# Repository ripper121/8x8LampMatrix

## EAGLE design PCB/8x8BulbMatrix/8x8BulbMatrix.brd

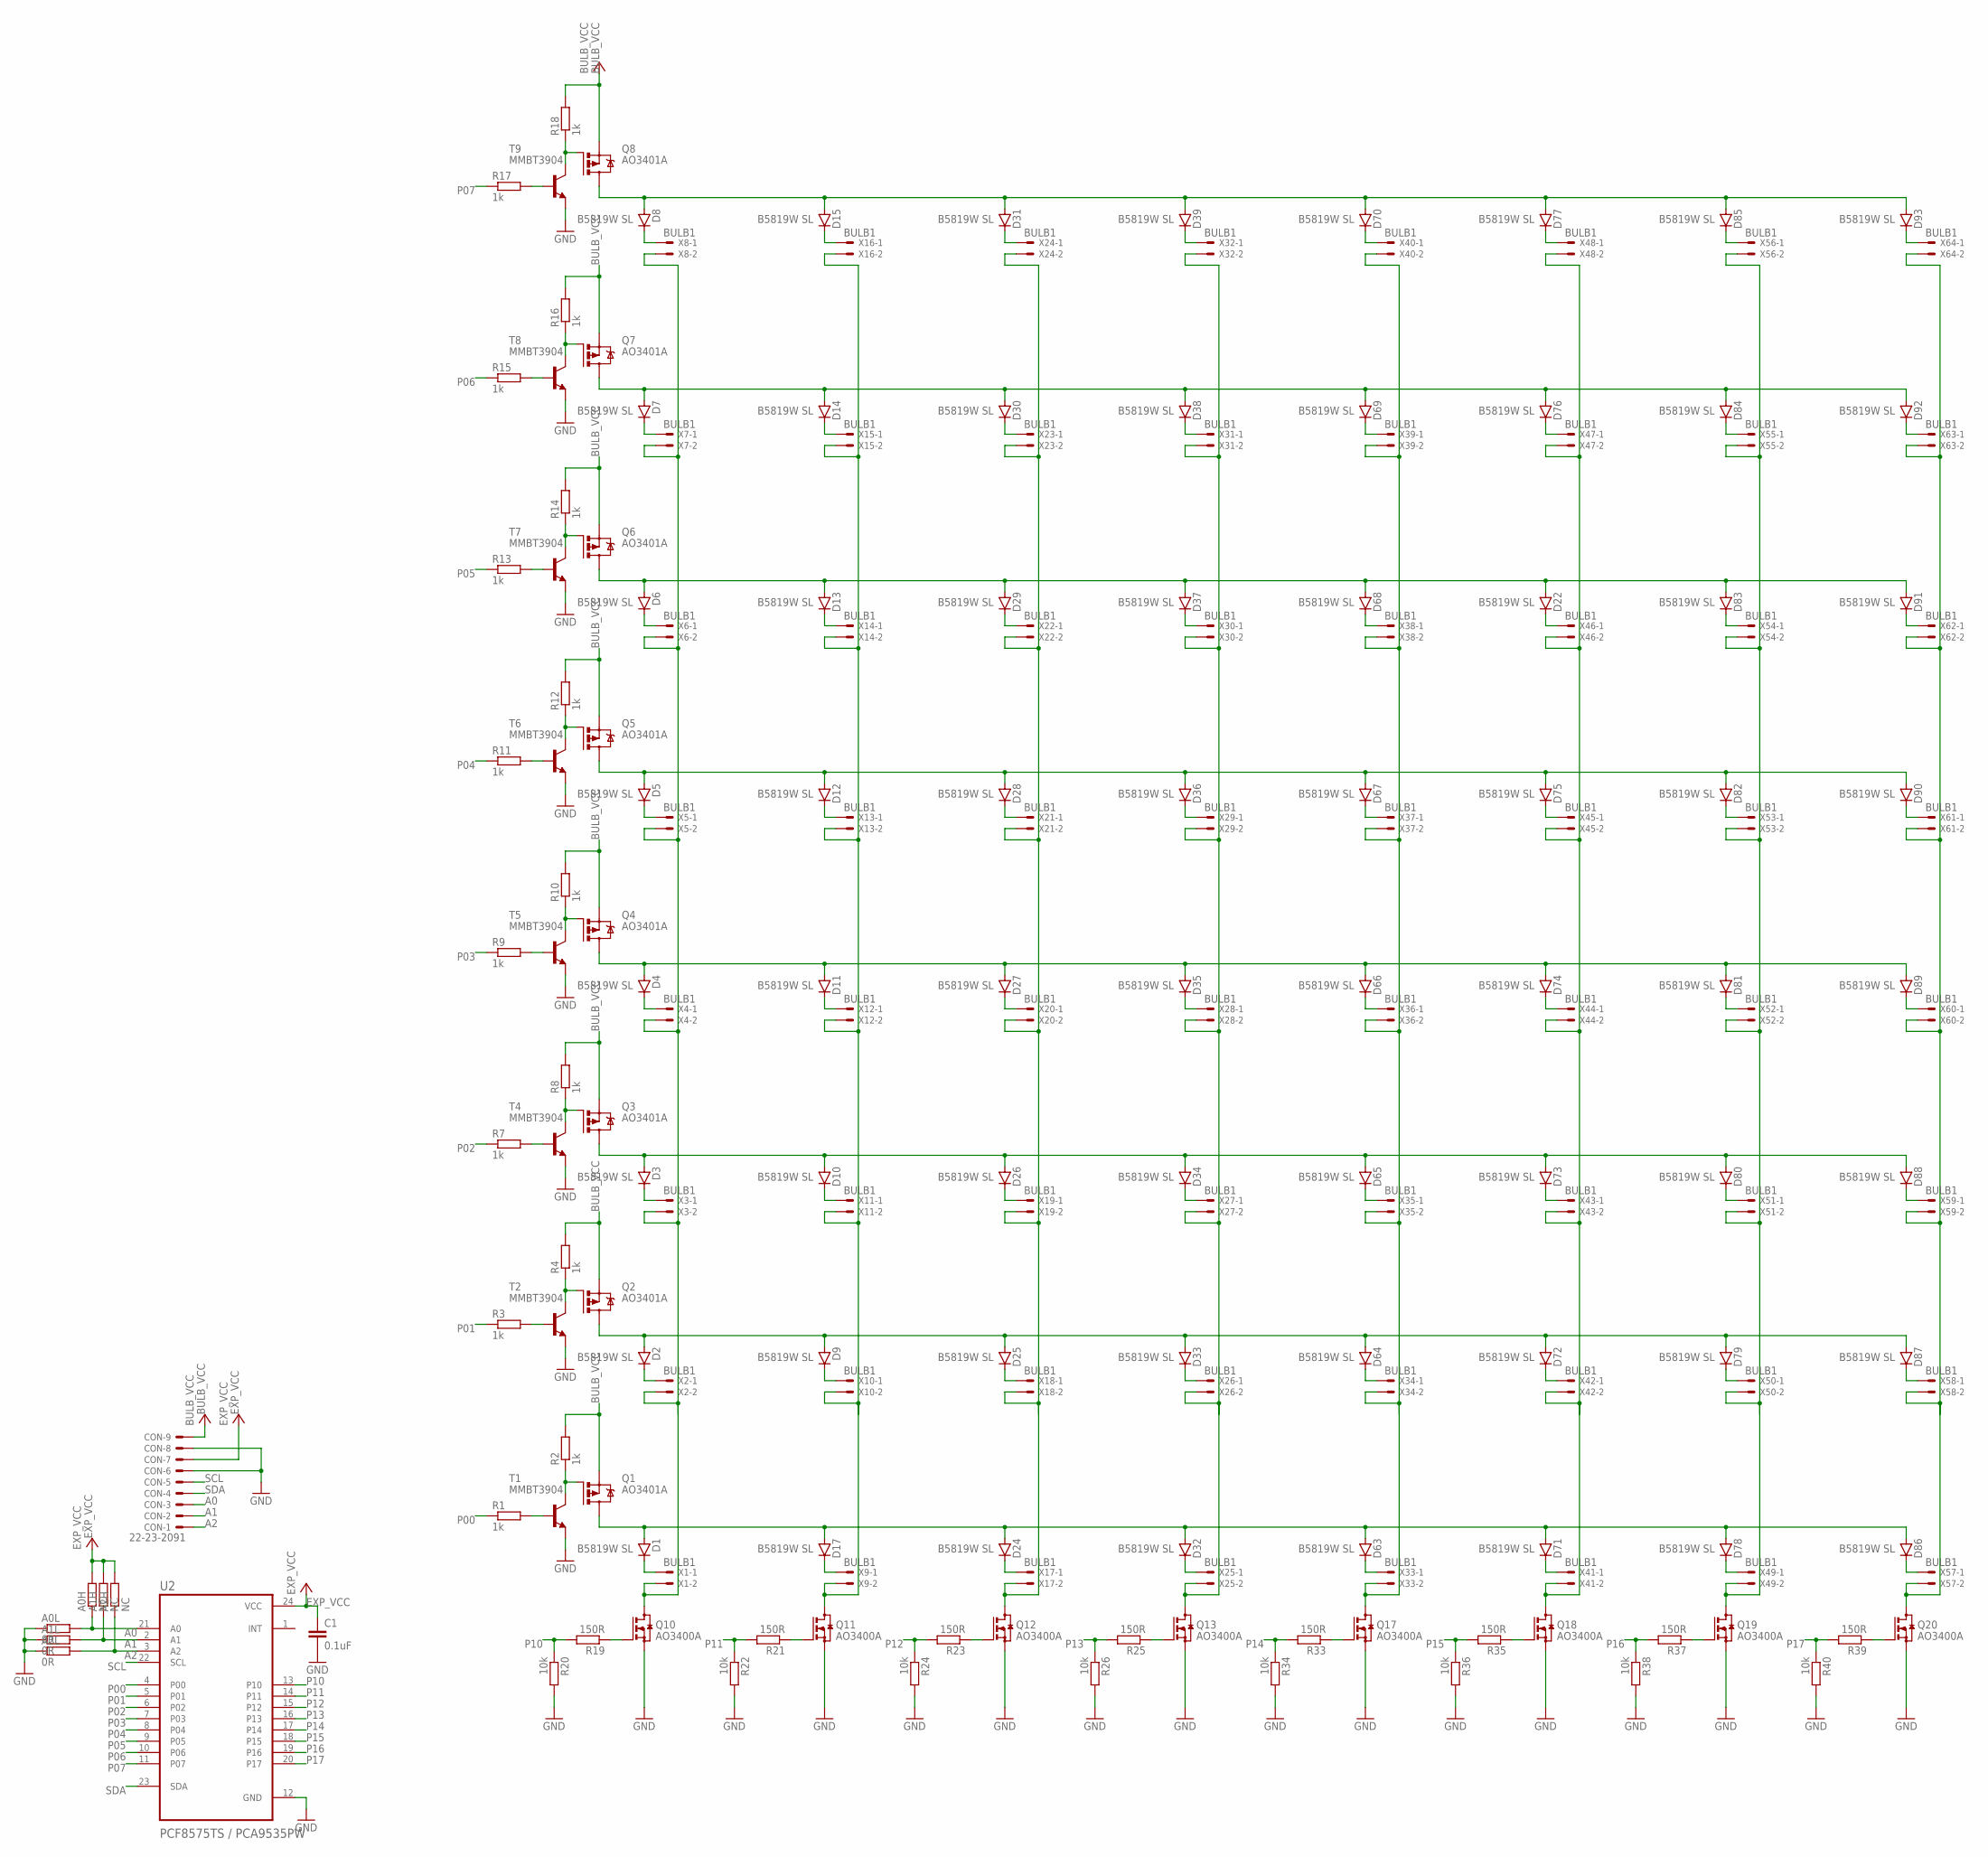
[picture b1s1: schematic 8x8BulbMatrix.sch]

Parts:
A0H, A1H, A2H: NC; R0603
A0L, A1L, A2L: 0R; R0603
C1: 0.1uF; C0805
CON: 22-23-2091
D1, D2, D3, D4, D5, D6, D7, D8, D9, D10, D11, D12, D13, D14, D15, D17, D22, D24, D25, D26, D27, D28, D29, D30, D31, D32, D33, D34, D35, D36, D37, D38, D39, D63, D64, D65, D66, D67, D68, D69, D70, D71, D72, D73, D74, D75, D76, D77, D78, D79, D80, D81, D82, D83, D84, D85, D86, D87, D88, D89, D90, D91, D92, D93: B5819W SL; SOD123
Q1, Q2, Q3, Q4, Q5, Q6, Q7, Q8: AO3401A; MICRO3
Q10, Q11, Q12, Q13, Q17, Q18, Q19, Q20: AO3400A; SOT23
R1, R2, R3, R4, R7, R8, R9, R10, R11, R12, R13, R14, R15, R16, R17, R18: 1k; R0603
R19, R21, R23, R25, R33, R35, R37, R39: 150R; R0603
R20, R22, R24, R26, R34, R36, R38, R40: 10k; R0603
T1, T2, T4, T5, T6, T7, T8, T9: MMBT3904; SOT23
U2: PCF8575TS / PCA9535PW; SOP65P780X200-24N
X1, X2, X3, X4, X5, X6, X7, X8, X9, X10, X11, X12, X13, X14, X15, X16, X17, X18, X19, X20, X21, X22, X23, X24, X25, X26, X27, X28, X29, X30, X31, X32, X33, X34, X35, X36, X37, X38, X39, X40, X41, X42, X43, X44, X45, X46, X47, X48, X49, X50, X51, X52, X53, X54, X55, X56, X57, X58, X59, X60, X61, X62, X63, X64: BULB1; 22-23-2021

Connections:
A0: A0H.1, A0L.2, CON.3, U2.21 (A0)
A1: A1H.1, A1L.2, CON.2, U2.2 (A1)
A2: A2H.1, A2L.2, CON.1, U2.3 (A2)
BULB_VCC: CON.9, Q1.2 (S), Q2.2 (S), Q3.2 (S), Q4.2 (S), Q5.2 (S), Q6.2 (S), Q7.2 (S), Q8.2 (S), R2.2, R4.2, R8.2, R10.2, R12.2, R14.2, R16.2, R18.2
EXP_VCC: A0H.2, A1H.2, A2H.2, C1.1, CON.7, U2.24 (VCC)
GND: A0L.1, A1L.1, A2L.1, C1.2, CON.6, CON.8, Q10.2 (S), Q11.2 (S), Q12.2 (S), Q13.2 (S), Q17.2 (S), Q18.2 (S), Q19.2 (S), Q20.2 (S), R20.2, R22.2, R24.2, R26.2, R34.2, R36.2, R38.2, R40.2, T1.2 (E), T2.2 (E), T4.2 (E), T5.2 (E), T6.2 (E), T7.2 (E), T8.2 (E), T9.2 (E), U2.12 (GND)
unnamed: Q10.3 (D), X1.2, X2.2, X3.2, X4.2, X5.2, X6.2, X7.2, X8.2
unnamed: D1.1 (C), X1.1
unnamed: R1.2, T1.1 (B)
unnamed: Q1.1 (G), R2.1, T1.3 (C)
unnamed: Q11.1 (G), R21.1
unnamed: R3.2, T2.1 (B)
unnamed: Q2.1 (G), R4.1, T2.3 (C)
unnamed: Q12.1 (G), R23.1
unnamed: D2.1 (C), X2.1
unnamed: D3.1 (C), X3.1
unnamed: Q13.1 (G), R25.1
unnamed: D4.1 (C), X4.1
unnamed: D5.1 (C), X5.1
unnamed: R7.2, T4.1 (B)
unnamed: D6.1 (C), X6.1
unnamed: Q3.1 (G), R8.1, T4.3 (C)
unnamed: D7.1 (C), X7.1
unnamed: Q10.1 (G), R19.1
unnamed: R9.2, T5.1 (B)
unnamed: D8.1 (C), X8.1
unnamed: Q4.1 (G), R10.1, T5.3 (C)
unnamed: R11.2, T6.1 (B)
unnamed: Q5.1 (G), R12.1, T6.3 (C)
unnamed: R13.2, T7.1 (B)
unnamed: Q6.1 (G), R14.1, T7.3 (C)
unnamed: R15.2, T8.1 (B)
unnamed: Q7.1 (G), R16.1, T8.3 (C)
unnamed: R17.2, T9.1 (B)
unnamed: Q8.1 (G), R18.1, T9.3 (C)
unnamed: D24.1 (C), X17.1
unnamed: Q12.3 (D), X17.2, X18.2, X19.2, X20.2, X21.2, X22.2, X23.2, X24.2
unnamed: D25.1 (C), X18.1
unnamed: D26.1 (C), X19.1
unnamed: D27.1 (C), X20.1
unnamed: D17.1 (C), X9.1
unnamed: Q11.3 (D), X9.2, X10.2, X11.2, X12.2, X13.2, X14.2, X15.2, X16.2
unnamed: D9.1 (C), X10.1
unnamed: D32.1 (C), X25.1
unnamed: D10.1 (C), X11.1
unnamed: D11.1 (C), X12.1
unnamed: D12.1 (C), X13.1
unnamed: D13.1 (C), X14.1
unnamed: D14.1 (C), X15.1
unnamed: D15.1 (C), X16.1
unnamed: Q13.3 (D), X25.2, X26.2, X27.2, X28.2, X29.2, X30.2, X31.2, X32.2
unnamed: D33.1 (C), X26.1
unnamed: D34.1 (C), X27.1
unnamed: D35.1 (C), X28.1
unnamed: D28.1 (C), X21.1
unnamed: D29.1 (C), X22.1
unnamed: D30.1 (C), X23.1
unnamed: D31.1 (C), X24.1
unnamed: D36.1 (C), X29.1
unnamed: D37.1 (C), X30.1
unnamed: D38.1 (C), X31.1
unnamed: D39.1 (C), X32.1
unnamed: D63.1 (C), X33.1
unnamed: Q17.3 (D), X33.2, X34.2, X35.2, X36.2, X37.2, X38.2, X39.2, X40.2
unnamed: D64.1 (C), X34.1
unnamed: D65.1 (C), X35.1
unnamed: D66.1 (C), X36.1
unnamed: D67.1 (C), X37.1
unnamed: D68.1 (C), X38.1
unnamed: D69.1 (C), X39.1
unnamed: D70.1 (C), X40.1
unnamed: Q17.1 (G), R33.1
unnamed: D71.1 (C), X41.1
unnamed: Q18.3 (D), X41.2, X42.2, X43.2, X44.2, X45.2, X46.2, X47.2, X48.2
unnamed: D72.1 (C), X42.1
unnamed: D73.1 (C), X43.1
unnamed: D74.1 (C), X44.1
unnamed: D75.1 (C), X45.1
unnamed: D22.1 (C), X46.1
unnamed: D76.1 (C), X47.1
unnamed: D77.1 (C), X48.1
unnamed: Q18.1 (G), R35.1
unnamed: D78.1 (C), X49.1
unnamed: Q19.3 (D), X49.2, X50.2, X51.2, X52.2, X53.2, X54.2, X55.2, X56.2
unnamed: D79.1 (C), X50.1
unnamed: D80.1 (C), X51.1
unnamed: D81.1 (C), X52.1
unnamed: D82.1 (C), X53.1
unnamed: D83.1 (C), X54.1
unnamed: D84.1 (C), X55.1
unnamed: D85.1 (C), X56.1
unnamed: Q19.1 (G), R37.1
unnamed: D86.1 (C), X57.1
unnamed: Q20.3 (D), X57.2, X58.2, X59.2, X60.2, X61.2, X62.2, X63.2, X64.2
unnamed: D1.2 (A), D17.2 (A), D24.2 (A), D32.2 (A), D63.2 (A), D71.2 (A), D78.2 (A), D86.2 (A), Q1.3 (D)
unnamed: D87.1 (C), X58.1
unnamed: D2.2 (A), D9.2 (A), D25.2 (A), D33.2 (A), D64.2 (A), D72.2 (A), D79.2 (A), D87.2 (A), Q2.3 (D)
unnamed: D88.1 (C), X59.1
unnamed: D89.1 (C), X60.1
unnamed: D90.1 (C), X61.1
unnamed: D91.1 (C), X62.1
unnamed: D92.1 (C), X63.1
unnamed: D93.1 (C), X64.1
unnamed: D3.2 (A), D10.2 (A), D26.2 (A), D34.2 (A), D65.2 (A), D73.2 (A), D80.2 (A), D88.2 (A), Q3.3 (D)
unnamed: D4.2 (A), D11.2 (A), D27.2 (A), D35.2 (A), D66.2 (A), D74.2 (A), D81.2 (A), D89.2 (A), Q4.3 (D)
unnamed: D5.2 (A), D12.2 (A), D28.2 (A), D36.2 (A), D67.2 (A), D75.2 (A), D82.2 (A), D90.2 (A), Q5.3 (D)
unnamed: D6.2 (A), D13.2 (A), D22.2 (A), D29.2 (A), D37.2 (A), D68.2 (A), D83.2 (A), D91.2 (A), Q6.3 (D)
unnamed: D7.2 (A), D14.2 (A), D30.2 (A), D38.2 (A), D69.2 (A), D76.2 (A), D84.2 (A), D92.2 (A), Q7.3 (D)
unnamed: D8.2 (A), D15.2 (A), D31.2 (A), D39.2 (A), D70.2 (A), D77.2 (A), D85.2 (A), D93.2 (A), Q8.3 (D)
unnamed: Q20.1 (G), R39.1
P00: R1.1, U2.4 (P00)
P01: R3.1, U2.5 (P01)
P02: R7.1, U2.6 (P02)
P03: R9.1, U2.7 (P03)
P04: R11.1, U2.8 (P04)
P05: R13.1, U2.9 (P05)
P06: R15.1, U2.10 (P06)
P07: R17.1, U2.11 (P07)
P10: R19.2, R20.1, U2.13 (P10)
P11: R21.2, R22.1, U2.14 (P11)
P12: R23.2, R24.1, U2.15 (P12)
P13: R25.2, R26.1, U2.16 (P13)
P14: R33.2, R34.1, U2.17 (P14)
P15: R35.2, R36.1, U2.18 (P15)
P16: R37.2, R38.1, U2.19 (P16)
P17: R39.2, R40.1, U2.20 (P17)
SCL: CON.5, U2.22 (SCL)
SDA: CON.4, U2.23 (SDA)

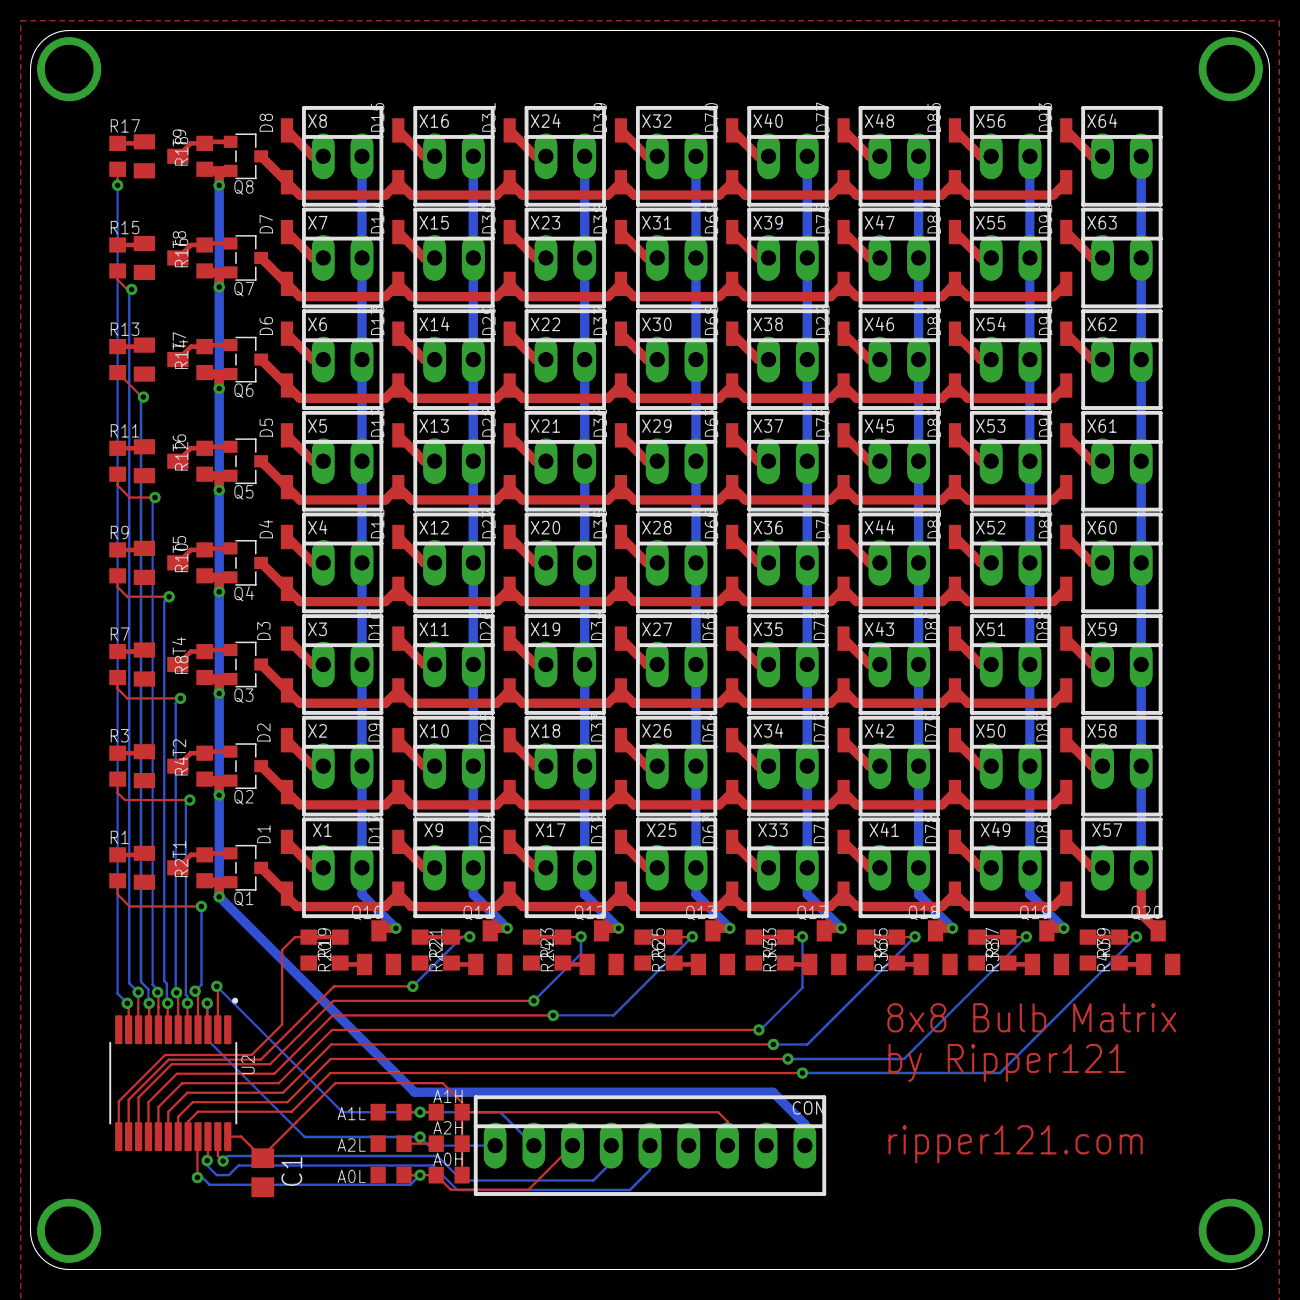
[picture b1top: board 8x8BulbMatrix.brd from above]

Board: 2 copper layers, 81.3 x 81.3 mm, 193 parts (0 on the bottom side), 128 nets.

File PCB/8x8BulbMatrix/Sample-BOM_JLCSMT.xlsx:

Comment | Designator | Footprint | JLCPCB Part #（optional）
0.1uF | C1 | C0805
0R | A0L, A1L, A2L | R0603
10k | R20, R22, R24, R26, R34, R36, R38, R40 | R0603
150R | R19, R21, R23, R25, R33, R35, R37, R39 | R0603
1k | R1, R2, R3, R4, R7, R8, R9, R10, R11, R12, R13, R14, R15, R16, R17, R18 | R0603
AO3400A | Q10, Q11, Q12, Q13, Q17, Q18, Q19, Q20 | SOT23
AO3401A | Q1, Q2, Q3, Q4, Q5, Q6, Q7, Q8 | SOT23
B5819W SL | D1, D2, D3, D4, D5, D6, D7, D8, D9, D10, D11, D12, D13, D14, D15, D17, D22, D24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 | SOD123
MMBT3904 | T1, T2, T4, T5, T6, T7, T8, T9 | SOT23
PCF8575TS | U2 | SSOP24

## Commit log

2021-12-23 Added Proteus Simulation
